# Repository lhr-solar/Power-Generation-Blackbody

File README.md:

# :sunny: Blackbody - Environmental Sensing PCBs

- [:sunny: Blackbody - Environmental Sensing PCBs](#sunny-blackbody---environmental-sensing-pcbs)
  - [Repository Structure](#repository-structure)

---

## Repository Structure

- **blackbody_a** - Sensing board for on-vehicle RTDs and irradiance sensors.
- **blackbody_b** - Sensing board for test setup irradiance measurements.
- **blackbody_c** - Topshell irradiance sensor breakout. Hooks up to Blackbody A.

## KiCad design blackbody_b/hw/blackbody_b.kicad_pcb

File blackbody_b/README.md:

# :sunny: Blackbody B - Sensing board for Test Setup Irradiance Measurements
- [:sunny: Blackbody B - Sensing board for Test Setup Irradiance Measurements](#sunny-blackbody-b---sensing-board-for-test-setup-irradiance-measurements)
  - [Repository Structure](#repository-structure)
  - [Maintainers](#maintainers)
  - [Versioning](#versioning)
  - [TODO](#todo)
    - [Documentation](#documentation)
    - [HW](#hw)
    - [SW](#sw)

---

## Repository Structure

- **datasheets** - contains datasheets for major components of the PCB.
- **docs** - contains documentation on how to build, test, and use the PCB.
- **fw** - contains fw that is loaded onto the PCB.
  - **tests** - test programs used to characterize and validate the PCB.
  - **src** - main program used to run the PCB.
  - **inc** - internally developed libraries specific for the PCB.
  - **lib** - third party libraries used by the PCB.
- **hw**
  - **footprints** - project specfic footprint association files for the PCB.
  - **models** - 3d .step files for the PCB 3d viewer.
  - **symbols** - project specific symbol files for the PCB.
  - **vX.Y.Z** - frozen versioning folder for PCB production files.
  - design files

---

## Maintainers

The current maintainer of this project is Matthew Yu as of 09/17/2023. His email
is [matthewjkyu@gmail.com](matthewjkyu@gmail.com).

Contributors to the HW and FW encompass many dedicated students, including:

- Jacob Pustilnik

Special thanks to Professor Gary Hallock, who supervised the development and
design of this project.

---

## Versioning

This PCB is on unified version `0.2.0`. Every time the schematic and/or layout
is updated, this version number should go up. We use [semantic
versioning](https://semver.org/) to denote between versions. See the
[changelog](./docs/CHANGELOG.md) for more details.

---

## TODO

### Documentation

- Update the following documents:
  - [Ordering and assembly](./docs/ORDERING_AND_ASSEMBLY.md)

### HW

- See [changelog 1.0.0rc](./docs/CHANGELOG.md#100rc-proposed) proposed changes to improve board cost, size.

### SW

- Validate final production program, in particular regards to CAN control.
- Add optional serial PC control.
- Calibrate TSL2591 light sensor for expected lighting conditions.
- Point all mbed-os references to fw/lib.

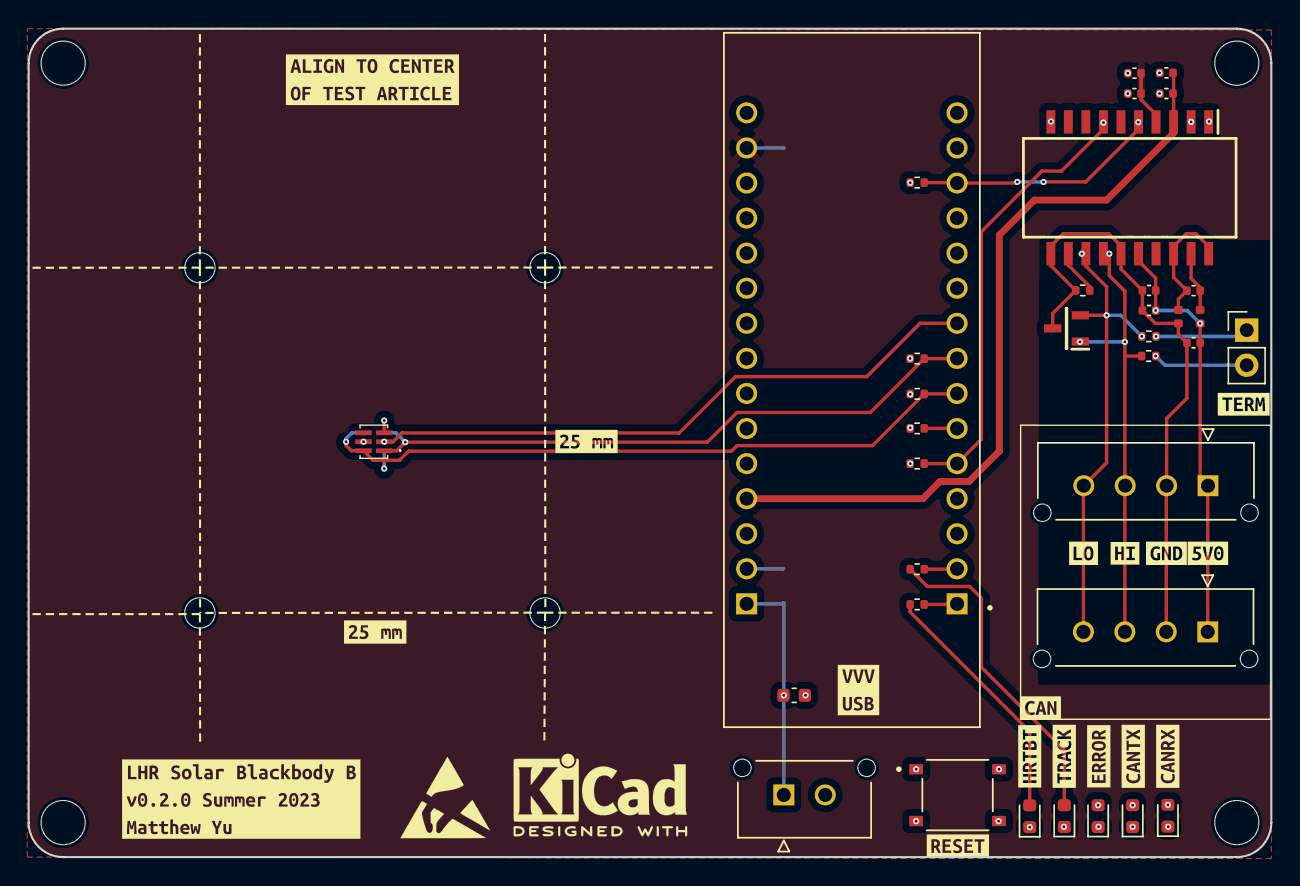
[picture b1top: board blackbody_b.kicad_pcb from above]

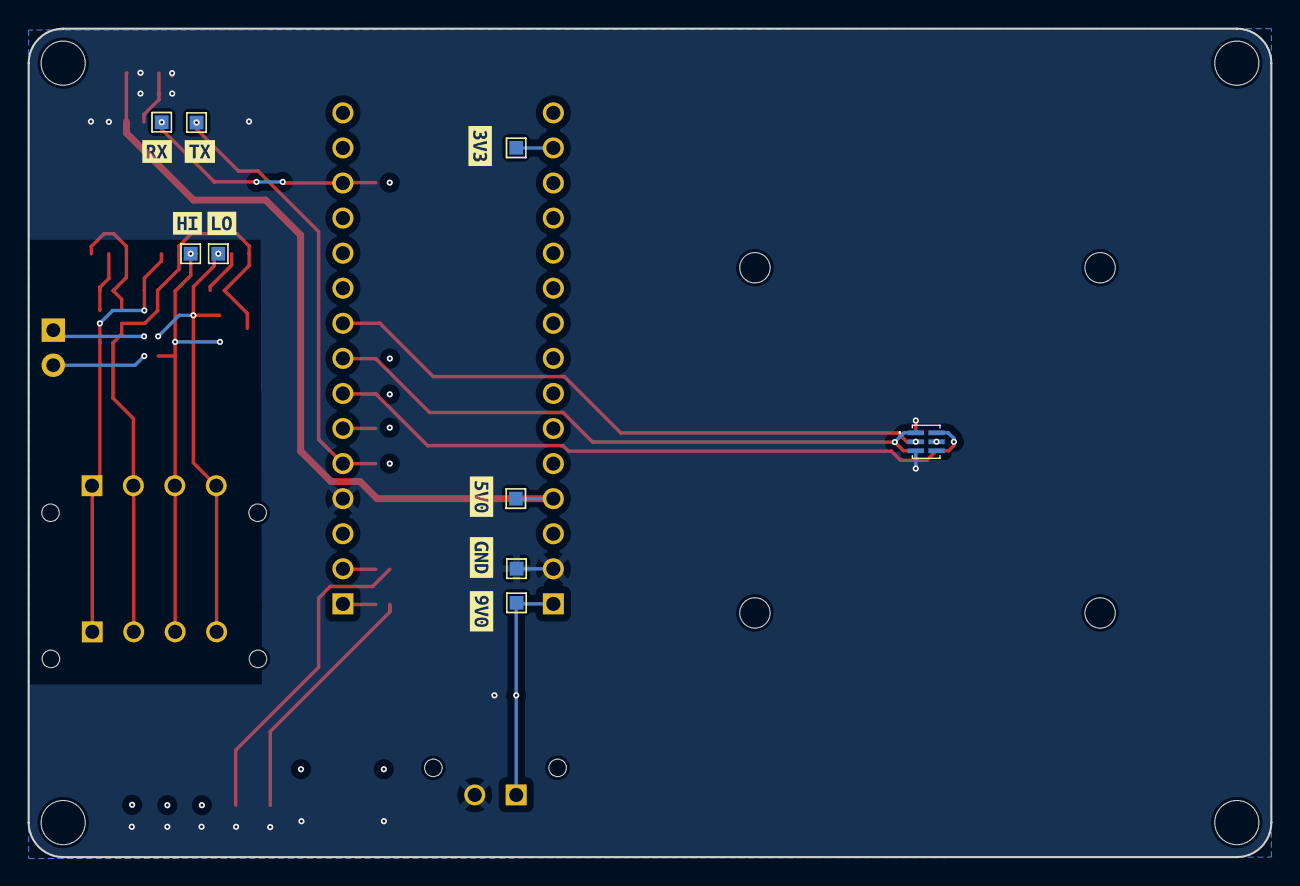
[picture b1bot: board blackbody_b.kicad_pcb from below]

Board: 4 copper layers, 90.0 x 60.0 mm, 77 parts (17 on the bottom side), 27 nets.

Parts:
C101: 10uF; C_0603_1608Metric
C201, C206: 10uF; C_0402_1005Metric
C202, C203, C208: 100nF; C_0402_1005Metric
C204, C207: 10nF; C_0402_1005Metric
C205: 220nF; C_0402_1005Metric
D101: YELLOW; LED_0603_1608Metric
D102, D103: GREEN; LED_0603_1608Metric
D104, D105: BLUE; LED_0603_1608Metric
D201: CDSOT23-T24CAN; bourns_CDSOT23_T24CAN
FID101, FID102, FID103, FID104: Fiducial; MountingHole_2.2mm_M2
H101, H102, H103, H104: MountingHole; MountingHole_3.2mm_M3
IC101, IC102: TSL25911FN; ams_TSL25911FN
IC201: ADM3055EBRIZ; analog_ADM3055EBRIZ
J101: 43650-0227; molex_microfit_43650_0227
J201, J202: 43650-0427; molex_microfit_43650_0427
JP201: Termination Resistors; PinHeader_1x02_P2.54mm_Vertical
L201, L202: 1.8k; L_0402_1005Metric
R101, R103: 4.7k; R_0402_1005Metric
R102, R104, R105, R106, R107: 100; R_0402_1005Metric
R201: 0; R_0402_1005Metric
R202, R203: 60.4; R_0402_1005Metric
S101: TS-1187A-B-A-B; xkb_TS_1187A_B_A_B
TP101: 3.3V TP; TestPoint_Pad_1.0x1.0mm
TP102: 5V TP; TestPoint_Pad_1.0x1.0mm
TP103: GND TP; TestPoint_Pad_1.0x1.0mm
TP104: 9V TP; TestPoint_Pad_1.0x1.0mm
TP201: CAN RX TP; TestPoint_Pad_1.0x1.0mm
TP202: CAN TX TP; TestPoint_Pad_1.0x1.0mm
TP203: CAN L TP; TestPoint_Pad_1.0x1.0mm
TP204: CAN H TP; TestPoint_Pad_1.0x1.0mm
U101: NUCLEO-L432KC; stm_nucleo_L432KC
kibuzzard-64E0E9DC: G***; kibuzzard-64E0E9DC
kibuzzard-64E0E9E4: G***; kibuzzard-64E0E9E4
kibuzzard-64E0E9FB: G***; kibuzzard-64E0E9FB
kibuzzard-64E0EA0A: G***; kibuzzard-64E0EA0A
kibuzzard-64E0EA02: G***; kibuzzard-64E0EA02
kibuzzard-64E0EA10: G***; kibuzzard-64E0EA10
kibuzzard-64E0EA63: G***; kibuzzard-64E0EA63
kibuzzard-64E0EAD5: G***; kibuzzard-64E0EAD5
kibuzzard-64E0EAF3, kibuzzard-64E0EAF3#2: G***; kibuzzard-64E0EAF3
kibuzzard-64E0EAFD: G***; kibuzzard-64E0EAFD
kibuzzard-64E0EB3C: G***; kibuzzard-64E0EB3C
kibuzzard-64E0EB4F: G***; kibuzzard-64E0EB4F
kibuzzard-64E0EB06: G***; kibuzzard-64E0EB06
kibuzzard-64E0EB26: G***; kibuzzard-64E0EB26
kibuzzard-64E0EB48: G***; kibuzzard-64E0EB48
kibuzzard-64E0EB63: G***; kibuzzard-64E0EB63
kibuzzard-64E0EB95, kibuzzard-64E0EB95#2: G***; kibuzzard-64E0EB95
kibuzzard-64E0EBC2: G***; kibuzzard-64E0EBC2
kibuzzard-64E0EBCA: G***; kibuzzard-64E0EBCA
kibuzzard-64E0F3D1: G***; kibuzzard-64E0F3D1
kibuzzard-64E0F3E7: G***; kibuzzard-64E0F3E7
kibuzzard-64E0F3F9, kibuzzard-64E0F3F9#2: G***; kibuzzard-64E0F3F9

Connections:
+3V3: C203.1, C204.1, IC101.5 (VDD), IC102.5 (VDD), IC201.4 (VIO), R101.1, R103.1, TP101.1, U101.17 (+3V3)
+5V: C201.1, C202.1, IC201.3 (VCC), TP102.1, U101.27 (+5V)
+9V: C101.1, J101.1, TP104.1, U101.30 (VIN)
/CAN_RX: IC201.5 (RXD), R107.2, TP201.1, U101.13 (D10)
/CAN_TX: IC201.7 (TXD), R106.2, TP202.1, U101.5 (D2)
/Error: R102.2, U101.6 (D3)
/Heartbeat: R105.2, U101.1 (D1)
/INT: IC101.2 (INT), IC102.2 (INT), U101.9 (D6)
/Reset: S101.A, S101.B, U101.3 (RST), U101.28 (RST)
/SCL: IC101.1 (SCL), IC102.1 (SCL), R101.2, U101.8 (D5)
/SDA: IC101.6 (SDA), IC102.6 (SDA), R103.2, U101.7 (D4)
/Tracking: R104.2, U101.2 (D0)
/comm_can/CAN_H: D201.1 (K1), IC201.14 (CANH), J201.3, J202.3, R202.2, TP204.1
/comm_can/CAN_L: D201.2 (K2), IC201.13 (CANL), J201.4, J202.4, R203.2, TP203.1
GND: C101.2, C201.2, C202.2, C203.2, C204.2, D101.1 (K), D102.1 (K), D103.1 (K), D104.1 (K), D105.1 (K), IC101.3 (GND), IC102.3 (GND), IC201.1 (GND1_1), IC201.2 (GND1_2), IC201.10 (GND1_3), J101.2, S101.C, S101.D, TP103.1, U101.4 (GND), U101.29 (GND)
unnamed: D101.2 (A), R102.1
unnamed: D102.2 (A), R104.1
unnamed: D103.2 (A), R105.1
unnamed: D104.2 (A), R106.1
unnamed: D105.2 (A), R107.1
unnamed: C206.2, C207.2, C208.2, D201.3 (K3), IC201.11 (GND2_1), IC201.15 (GND2_2), J201.2, J202.2, L202.1, R201.2
unnamed: C205.2, IC201.18 (GNDISO_1), IC201.20 (GNDISO_2), L202.2
unnamed: IC201.12 (RS), R201.1
unnamed: C206.1, C207.1, C208.1, IC201.16 (VISOIN), J201.1, J202.1, L201.1
unnamed: C205.1, IC201.19 (VISOOUT), L201.2
unnamed: JP201.1 (A), R203.1
unnamed: JP201.2 (B), R202.1

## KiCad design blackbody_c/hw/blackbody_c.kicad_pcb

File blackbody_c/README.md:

# :sunny: Blackbody C - Topshell Irradiance Sensor Breakout

- [:sunny: Blackbody C - Topshell Irradiance Sensor Breakout](#sunny-blackbody-c---topshell-irradiance-sensor-breakout)
  - [Repository Structure](#repository-structure)
  - [Maintainers](#maintainers)
  - [Versioning](#versioning)
  - [TODO](#todo)
    - [Documentation](#documentation)
    - [HW](#hw)

---

## Repository Structure

- **datasheets** - contains datasheets for major components of the PCB.
- **docs** - contains documentation on how to build, test, and use the PCB.
- **fw** - contains fw that is loaded onto the PCB.
  - **tests** - test programs used to characterize and validate the PCB.
  - **src** - main program used to run the PCB.
  - **inc** - internally developed libraries specific for the PCB.
  - **lib** - third party libraries used by the PCB.
- **hw**
  - **footprints** - project specfic footprint association files for the PCB.
  - **models** - 3d .step files for the PCB 3d viewer.
  - **symbols** - project specific symbol files for the PCB.
  - **vX.Y.Z** - frozen versioning folder for PCB production files.
  - design files

---

## Maintainers

The current maintainer of this project is Matthew Yu as of 07/16/2023. His email
is [matthewjkyu@gmail.com](matthewjkyu@gmail.com).

Special thanks to Professor Gary Hallock, who supervised the development and
design of this project.

---

## Versioning

This PCB is on unified version `0.1.0`. Every time the schematic and/or layout
is updated, this version number should go up. We use [semantic
versioning](https://semver.org/) to denote between versions. See the
[changelog](./docs/CHANGELOG.md) for more details.

---

## TODO

### Documentation

- Update the following documents:
  - [Ordering and assembly](./docs/ORDERING_AND_ASSEMBLY.md)

### HW

- Make board revision as proposed by [changelog 1.0.0rc](./docs/CHANGELOG.md#100rc-proposed).

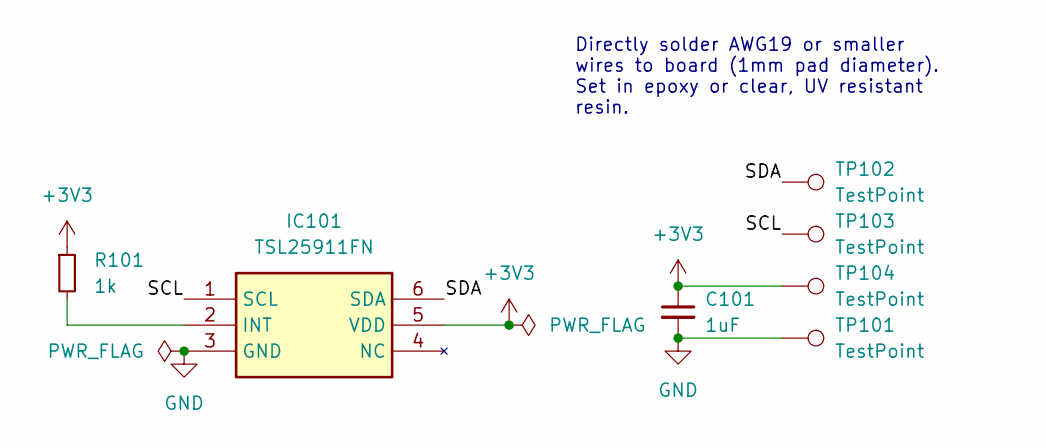
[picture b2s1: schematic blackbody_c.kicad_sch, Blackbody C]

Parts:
C101: 1uF; C_0402_1005Metric; LCSC Part # C52923
IC101: TSL25911FN; ams_TSL25911FN; Mouser Part Number 985-TSL25911FN
R101: 1k; R_0402_1005Metric; LCSC Part # C11702
TP101, TP102, TP103, TP104: TestPoint; TestPoint_Pad_1.0x1.0mm

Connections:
+3V3: C101.1, IC101.5 (VDD), R101.1, TP104.1
/SCL: IC101.1 (SCL), TP103.1
/SDA: IC101.6 (SDA), TP102.1
GND: C101.2, IC101.3 (GND), TP101.1
unnamed: IC101.2 (INT), R101.2

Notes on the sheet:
Directly solder AWG19 or smaller wires to board (1mm pad diameter). Set in epoxy or clear, UV resistant resin.

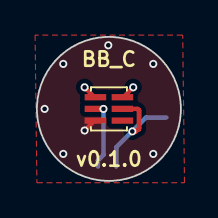
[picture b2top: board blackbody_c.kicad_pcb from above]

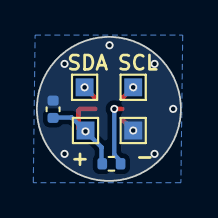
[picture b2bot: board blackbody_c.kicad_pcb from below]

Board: 2 copper layers, 8.0 x 8.0 mm, 7 parts (6 on the bottom side), 5 nets.

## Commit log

2023-07-17 initial commit with new revs for all boards. Consolidates Array-Blackbody-B-PCB, Array-Blackbody-A-PCB, Array_RTD_Controller, RTD_Array_Board, Blackbody, and Array-TSL2591PCB.
2023-07-17 README for main repo, update improvements with replacing nucleo w/ chip
2023-07-18 blackbody c revisions based on review
2023-07-22 screenshots
2023-08-01 fixes for blackbody b before prod
2023-08-19 update labels w/ kibuzzard, regen outputs
2023-09-16 initial test structure for blackbody A, test docs for blackbody
2023-09-18 blackbody B tests and main
2023-09-18 update documentation
2024-01-12 documentation, minor fix to code for bb-b
2024-02-10 Add files via upload
    main_v2 has the (in-progress) production code for blackbody A
2024-04-27 Add files via upload
    mainNoCan.cpp is the current version of the driver. Known Issues:
    - CAN sends from Nucleo fine to CAN transceiver, but transceiver doesn't seem to send a signal out
    - Previous code implementation with event queue seemed to have some issues with the RTD measuring not being threadsafe. For now, it is manually being delayed to the correct frequency, but making it t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
    - Using RTD4 will not allow the use of printf, so when debugging, comment out anything related to RTD4
    - RTD5 and 7 will not allow the irradiance sensor to measure unless a jumper 16 on the Nucleo is desoldered
2024-04-27 Uploaded Current Prod Code Version (See Comment)
    mainNoCan.cpp is the current version of the driver. Known Issues:
    - CAN sends from Nucleo fine to CAN transceiver, but transceiver doesn't seem to send a signal out
    - Previous code implementation with event queue seemed to have some issues with the RTD measuring not being threadsafe. For now, it is manually being delayed to the correct frequency, but making it t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
    - Using RTD4 will not allow the use of printf, so when debugging, comment out anything related to RTD4
    - RTD5 and 7 will not allow the irradiance sensor to measure unless a jumper 16 on th
2024-04-27 Current Prod Code in mainNoCan.cpp (See comments)
    mainNoCan.cpp is the current version of the driver. Known Issues:
    - CAN sends from Nucleo fine to CAN transceiver, but transceiver doesn't seem to send a signal out
    - Previous code implementation with event queue seemed to have some issues with the RTD measuring not being threadsafe. For now, it is manually being delayed to the correct frequency, but making it t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
    - Using RTD4 will not allow the use of printf, so when debugging, comment out anything related to RTD4
    - RTD5 and 7 will not allow the irradiance sensor to measure unless a jumper 16 on t
